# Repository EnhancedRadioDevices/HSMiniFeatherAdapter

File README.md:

HamShieldMini Feather Adapter Hardware

These are the hardware design files for the Adapter board that connects a HamShieldMini1.1 to an AdaFruit Feather nRF52840.

* HamShieldMini Hardware here: https://github.com/EnhancedRadioDevices/HamShieldMini
* HamShield (and Mini) Software here: https://github.com/EnhancedRadioDevices/HamShield
* Get a Feather here: https://www.adafruit.com/product/4062

These hardware files were created with KiCAD. 
You may need the KiCAD libraries available here: https://github.com/mogar/KiCAD_libs
When opening these projects in KiCAD, you may need to change the path to the libraries from the above link.
This can be done in preferences->libraries in both the schematic editor and the layout editor.
Make sure the libraries noted there point to wherever you put the above KiCAD_libs repo.

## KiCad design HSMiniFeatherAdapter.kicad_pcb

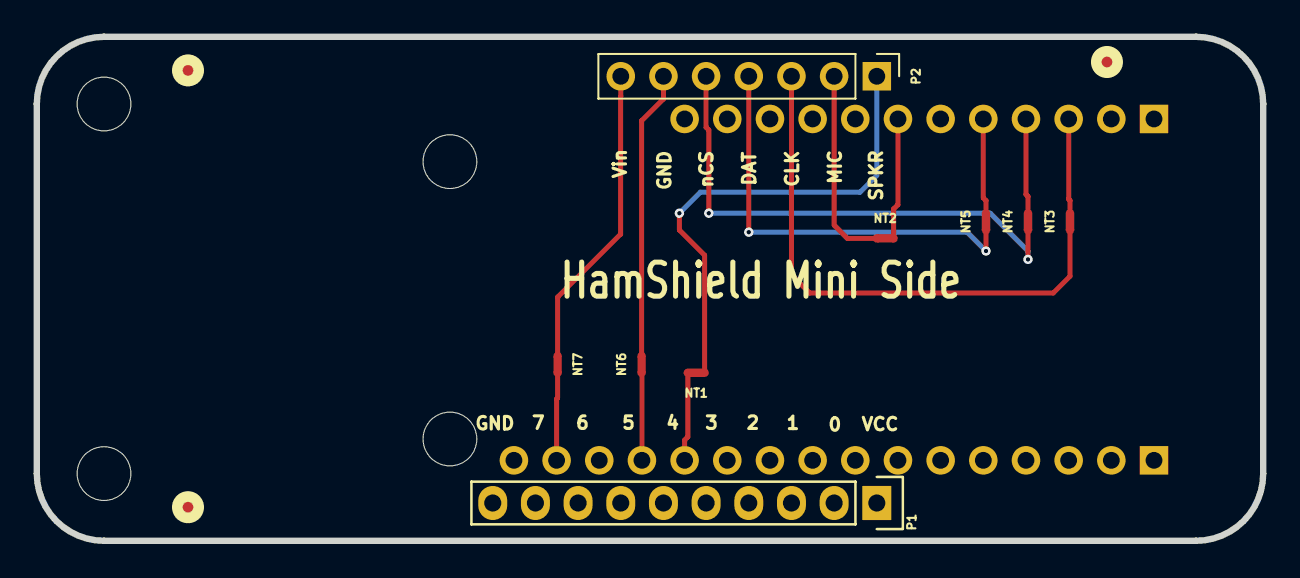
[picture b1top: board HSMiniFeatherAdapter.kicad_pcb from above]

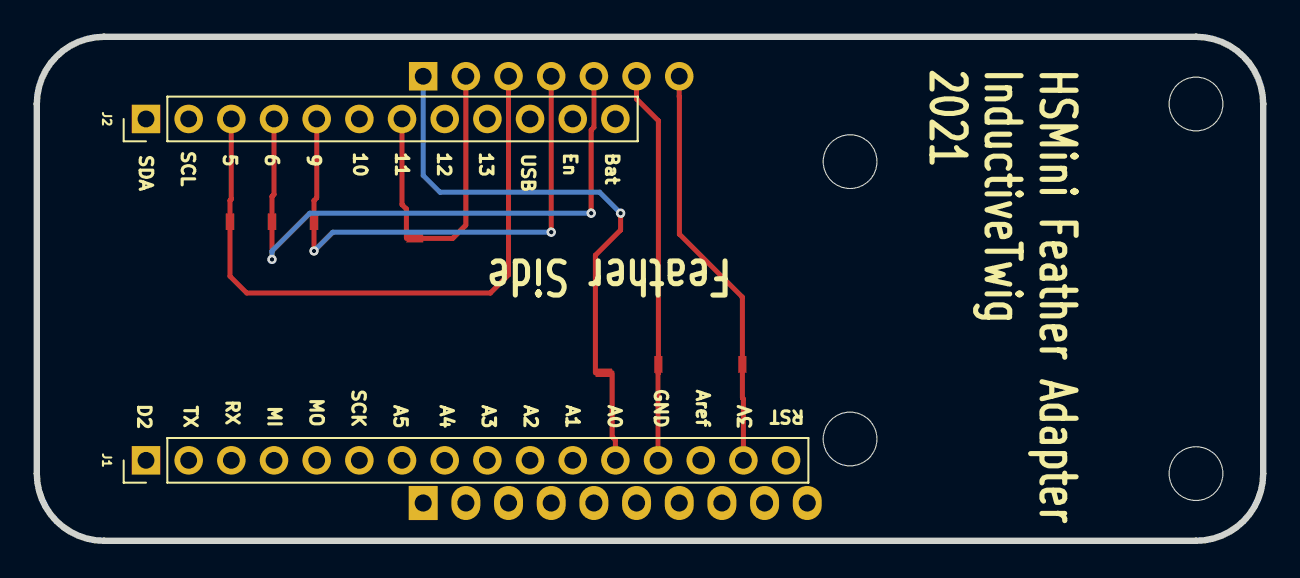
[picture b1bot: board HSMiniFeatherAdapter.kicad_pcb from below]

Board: 2 copper layers, 73.0 x 30.0 mm, 18 parts (2 on the bottom side), 13 nets.

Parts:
FD1, FD2, FD3: FIDUCIAL1X2.5; SparkFun-FIDUCIAL-1X2.5
J1: Conn_01x16; Pin_Header_Straight_1x16_Pitch2.54mm
J2: Conn_01x12; Pin_Header_Straight_1x12_Pitch2.54mm
MK1, MK2, MK3, MK4: MountingHole; MountingHole_3.2mm_M3
NT1, NT2, NT3, NT4, NT5, NT6, NT7: Net-Tie_2; NetTie-2_SMD_Pad0.5mm
P1: Conn_01x10; Pin_Header_Straight_1x10
P2: Conn_01x07; Pin_Header_Straight_1x07_Pitch2.54mm

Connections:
/3V: J1.15, NT7.2
/5: J2.3, NT3.2
/6: J2.4, NT4.2
/9: J2.5, NT5.2
/11: J2.7, NT2.2
/A0: J1.12, NT1.2
/ARD_AUDIO_OUT: NT1.1, P2.1
/CLK: NT3.1, P2.3
/DAT: NT5.1, P2.4
/PWM_AUDIO_IN: NT2.1, P2.2
/nCS: NT4.1, P2.5
GND: J1.13, NT6.1, NT6.2, P1.10, P2.6
VIN: NT7.1, P2.7

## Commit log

2021-08-15 :lollipop: Added .gitattributes
2021-08-15 Adding design files
2021-08-15 Update README.md
    Update project info.
